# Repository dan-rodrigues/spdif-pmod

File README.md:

# S/PDIF PMOD

This is a PMOD that provides S/PDIF compatible coaxial and optical outputs.

The coaxial output does not use a pulse transformer. A DA101(J)C or similar can be easily added if needed.

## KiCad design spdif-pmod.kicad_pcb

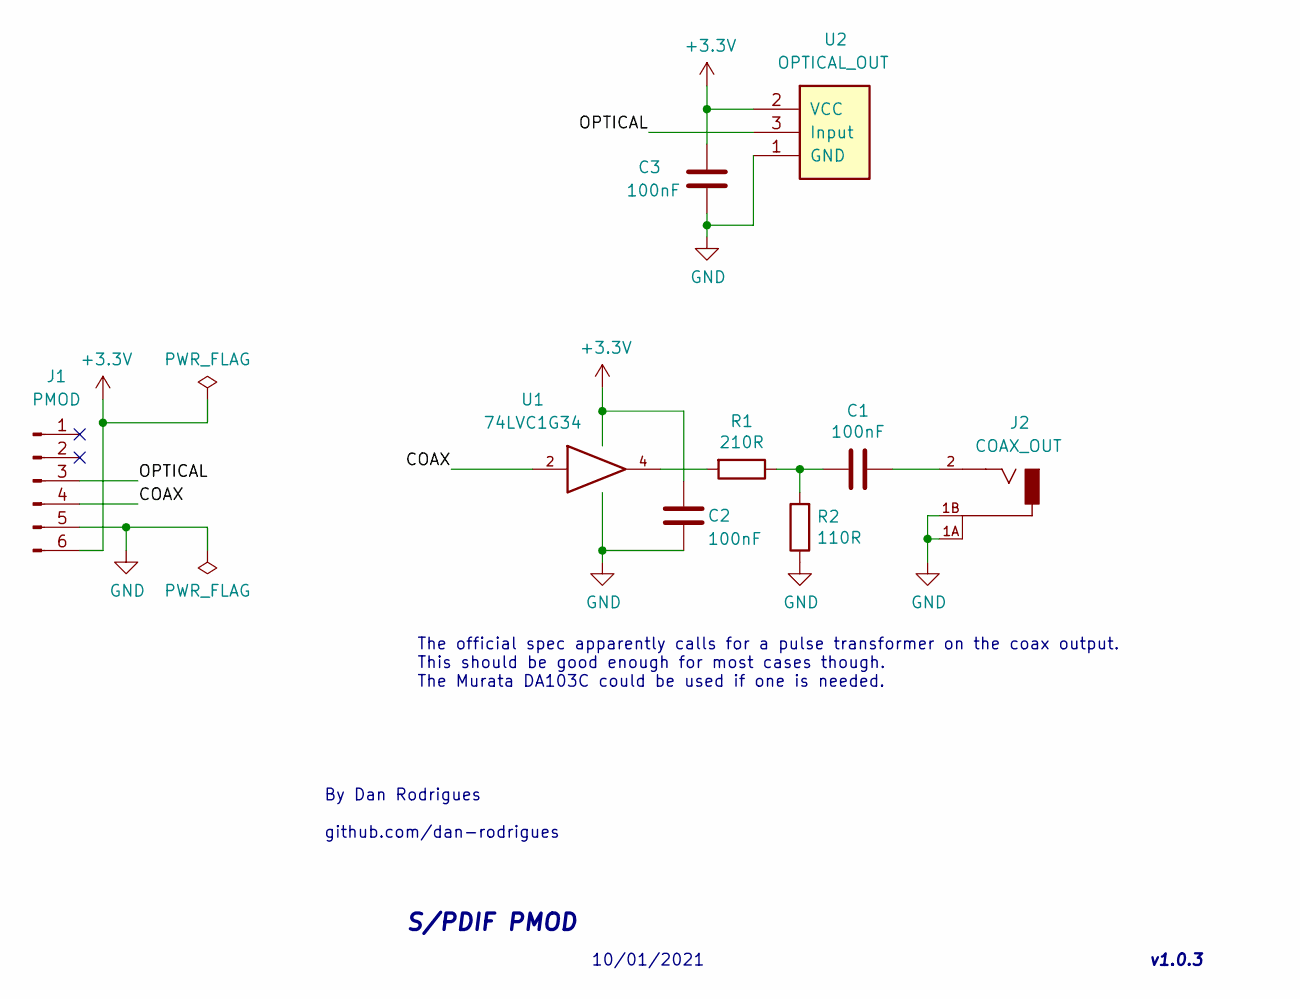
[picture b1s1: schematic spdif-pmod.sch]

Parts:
C1, C2, C3: 100nF; C_0603_1608Metric_Pad1.08x0.95mm_HandSolder
J1: PMOD; PinHeader_1x06_P2.54mm_Horizontal
J2: COAX_OUT; RCJ-02x
R1: 210R; R_0603_1608Metric_Pad0.98x0.95mm_HandSolder
R2: 110R; R_0603_1608Metric_Pad0.98x0.95mm_HandSolder
U1: 74LVC1G34; SOT-353_SC-70-5_Handsoldering
U2: OPTICAL_OUT; FCR684208T

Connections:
+3V3: C2.1, C3.1, J1.6, U1.5 (VCC), U2.2 (VCC)
/COAX: J1.4, U1.2
/OPTICAL: J1.3, U2.3 (Input)
GND: C2.2, C3.2, J1.5, J2.1A, J2.1B, R2.1, U1.3 (GND), U2.1 (GND)
unnamed: C1.1, R1.1, R2.2
unnamed: C1.2, J2.2
unnamed: R1.2, U1.4

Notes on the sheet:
S/PDIF PMOD
10/01/2021
v1.0.3
The official spec apparently calls for a pulse transformer on the coax output. This should be good enough for most cases though. The Murata DA103C could be used if one is needed.
By Dan Rodrigues github.com/dan-rodrigues

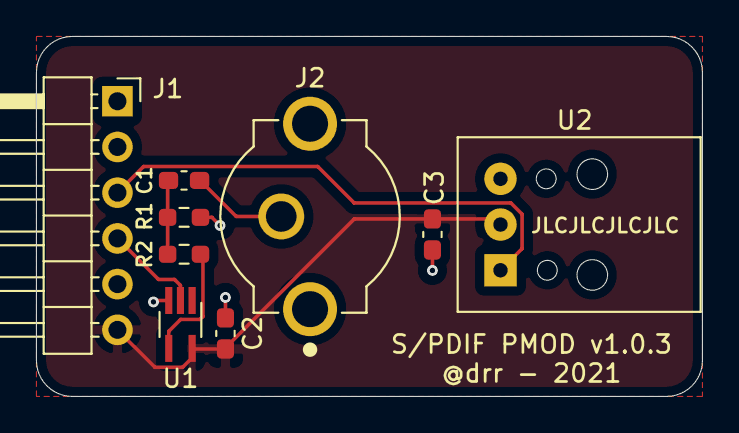
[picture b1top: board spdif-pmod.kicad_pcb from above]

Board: 2 copper layers, 37.0 x 20.0 mm, 9 parts (0 on the bottom side), 7 nets.

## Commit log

2021-02-27 Restore repo
2021-02-28 Correct Murata part that would be used instead
